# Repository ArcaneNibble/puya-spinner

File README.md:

# PY32 fidget spinner demo

This is a quick-and-dirty demo of _just_ how cheap embedded compute can get nowadays &mdash; approximately USD$6 for an *assembled* board with a 32-bit Cortex-M0.

In order to actually make good use of this available compute, the idea was to build a modern (i.e. state-space) control theory estimator to determine the orientation of the fidget spinner from accelerometer data, rather than more traditional approaches involving hall effect sensors.

## Status

Revision A was ordered from JLCPCB, and all of the essential components work.

The state estimator has yet to be written, as the author is aphantasic and not much of a shape rotator (and thus struggling with writing out the necessary "physical world" equations).

## Main components

* PY32F002AL15 (MCU)
* SC7A20 (accelerometer)
* CR2032 battery
* 30 charlieplexed LEDs

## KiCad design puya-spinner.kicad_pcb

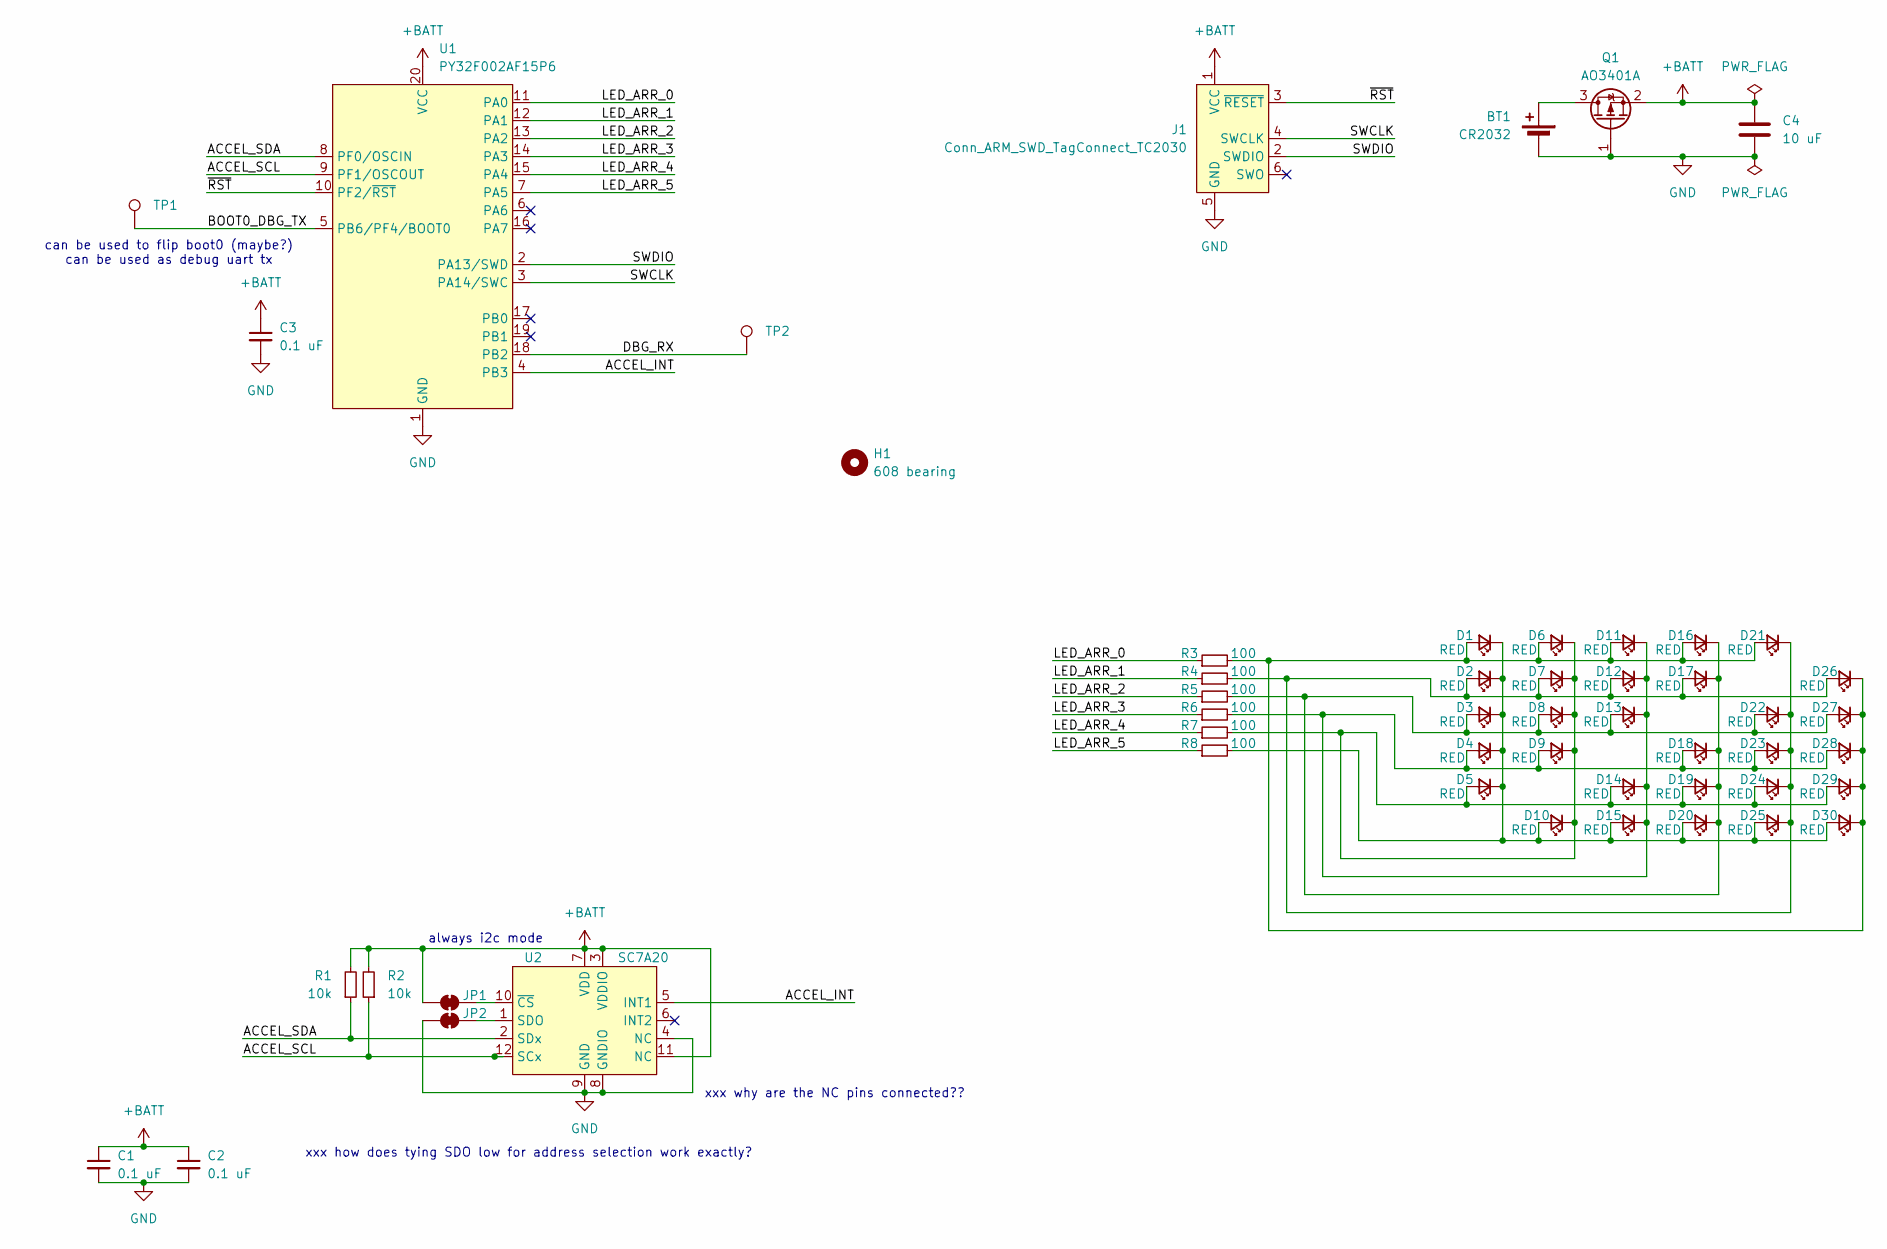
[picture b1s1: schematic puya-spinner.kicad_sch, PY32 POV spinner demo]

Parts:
BT1: CR2032; Battery_MYOUNG_BS-07-A1BJ001_CR2032; LCSC C2979167
C1, C2, C3: 0.1 uF; C_0402_1005Metric; LCSC C1525
C4: 10 uF; C_1206_3216Metric; LCSC C13585
D1, D2, D3, D4, D5, D6, D7, D8, D9, D10, D11, D12, D13, D14, D15, D16, D17, D18, D19, D20, D21, D22, D23, D24, D25, D26, D27, D28, D29, D30: RED; LED_0603_1608Metric; LCSC C2286
H1: 608 bearing; fixme_608_bearing
J1: Conn_ARM_SWD_TagConnect_TC2030; Tag-Connect_TC2030-IDC-FP_2x03_P1.27mm_Vertical
JP1, JP2: SolderJumper_2_Bridged; SolderJumper-2_P1.3mm_Bridged_RoundedPad1.0x1.5mm
Q1: AO3401A; SOT-23; LCSC C15127
R1, R2: 10k; R_0402_1005Metric; LCSC C25744
R3, R4, R5, R6, R7, R8: 100; R_0402_1005Metric; LCSC C25076
TP1, TP2: TestPoint; TestPoint_Pad_2.0x2.0mm
U1: PY32F002AF15P6; TSSOP-20_4.4x6.5mm_P0.65mm; LCSC C5292059
U2: SC7A20; LGA-12_2x2mm_P0.5mm; LCSC C5126709

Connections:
+BATT: C1.1, C2.1, C3.1, C4.1, J1.1 (VCC), JP1.1 (A), Q1.2 (S), R1.2, R2.2, U1.20 (VCC), U2.3 (VDDIO), U2.7 (VDD), U2.11 (NC)
/ACCEL_INT: U1.4 (PB3), U2.5 (INT1)
/ACCEL_SCL: R2.1, U1.9 (PF1/OSCOUT), U2.12 (SCx)
/ACCEL_SDA: R1.1, U1.8 (PF0/OSCIN), U2.2 (SDx)
/BOOT0_DBG_TX: TP1.1, U1.5 (PB6/PF4/BOOT0)
/DBG_RX: TP2.1, U1.18 (PB2)
/LED_ARR_0: R3.1, U1.11 (PA0)
/LED_ARR_1: R4.1, U1.12 (PA1)
/LED_ARR_2: R5.1, U1.13 (PA2)
/LED_ARR_3: R6.1, U1.14 (PA3)
/LED_ARR_4: R7.1, U1.15 (PA4)
/LED_ARR_5: R8.1, U1.7 (PA5)
/SWCLK: J1.4 (SWCLK), U1.3 (PA14/SWC)
/SWDIO: J1.2 (SWDIO), U1.2 (PA13/SWD)
/~RST: J1.3 (~RESET), U1.10 (PF2/~RST)
GND: BT1.2 (-), C1.2, C2.2, C3.2, C4.2, J1.5 (GND), JP2.1 (A), Q1.1 (G), U1.1 (GND), U2.4 (NC), U2.8 (GNDIO), U2.9 (GND)
unnamed: BT1.1 (+), Q1.3 (D)
unnamed: D1.2 (A), D6.2 (A), D11.2 (A), D16.2 (A), D21.2 (A), D26.1 (K), D27.1 (K), D28.1 (K), D29.1 (K), D30.1 (K), R3.2
unnamed: D1.1 (K), D2.1 (K), D3.1 (K), D4.1 (K), D5.1 (K), D10.2 (A), D15.2 (A), D20.2 (A), D25.2 (A), D30.2 (A), R8.2
unnamed: D5.2 (A), D6.1 (K), D7.1 (K), D8.1 (K), D9.1 (K), D10.1 (K), D14.2 (A), D19.2 (A), D24.2 (A), D29.2 (A), R7.2
unnamed: D4.2 (A), D9.2 (A), D11.1 (K), D12.1 (K), D13.1 (K), D14.1 (K), D15.1 (K), D18.2 (A), D23.2 (A), D28.2 (A), R6.2
unnamed: D2.2 (A), D7.2 (A), D12.2 (A), D17.2 (A), D21.1 (K), D22.1 (K), D23.1 (K), D24.1 (K), D25.1 (K), D26.2 (A), R4.2
unnamed: D3.2 (A), D8.2 (A), D13.2 (A), D16.1 (K), D17.1 (K), D18.1 (K), D19.1 (K), D20.1 (K), D22.2 (A), D27.2 (A), R5.2
unnamed: JP1.2 (B), U2.10 (~CS)
unnamed: JP2.2 (B), U2.1 (SDO)

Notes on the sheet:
always i2c mode
can be used to flip boot0 (maybe?) can be used as debug uart tx
xxx how does tying SDO low for address selection work exactly?
xxx why are the NC pins connected??

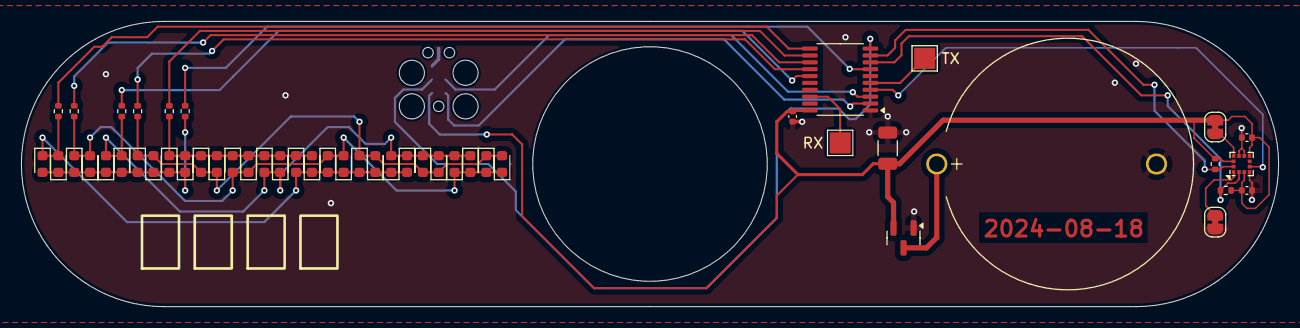
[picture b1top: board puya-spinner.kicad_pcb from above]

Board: 2 copper layers, 119.0 x 27.0 mm, 52 parts (1 on the bottom side), 25 nets.

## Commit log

2024-07-09 Add README
2024-07-09 add custom parts
2024-07-09 initial sch
2024-07-10 assign most parts
2024-07-10 add power flags; fix interrupt pin
2024-07-10 add battery holder footprint
2024-07-10 change no-connect pins
2024-07-10 FIXME add bearing
    need to change tolerances
2024-07-10 initial route
2024-07-10 tweaks; mostly to big capacitor
2024-07-10 mostly idle tweaks
2024-07-11 fix bearing hole; add reverse polarity protection
2024-07-11 some tweaks to make ground plane look nicer
2024-08-18 revA for fab
2024-08-27 Initial commit of fw
2024-08-27 fix linker cpu arch
2024-08-27 fix keeping vectors
2024-08-27 LED data entry, chaser pattern
2024-08-28 basic i2c test
2024-08-28 interrupt-driven i2c
2024-08-28 i2c multi read maybe working
2024-08-28 busticated again
2024-08-28 fucking what hate this device
2024-08-28 blah accel config
2024-08-28 accel interrupt pin works
2024-08-28 configure exti
2024-08-28 refactor out led code
2024-08-28 log accel data to buffer
2024-08-28 linking libm works
2024-08-28 vaguely working all the embedded bits
2024-09-03 Add 0BSD license
